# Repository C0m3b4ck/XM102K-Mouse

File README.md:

# XM102K Mouse in KiCAD 
[@PrinterFixer](https://www.youtube.com/@PrinterFixer)
[Video title here](VIDEO HERE - IF THERE IS NONE THEN IT IS NOT DONE)

KiCAD project with GERBER and DRILL files of the XM102K mouse PCB from 2012/02/03, remade manually by me, C0m3b4ck. All models of all components are in place, the PCB is of accurate size. The only inacurracies are the connections, which aren't 1:1 to the actual PCB. The microswitch and the rotary encoder are the exact same but from different companies (couldn't find original companies).

**The mouse PCB is from 2012/02/03. It is end-of-life and comes from an unknown Chinese manufacturer.** 

## Capabilities
**From the MX8733B documentation:**
* Optical Navigation Technology
* Universal Serial Bus Specification, version 2.0
* USB HID Specification, version 1.1
* USB-IF and WHQL compliable
* 5V Power Supply
* Power saving during no motion
* On chip LED drive with regulated current
* Crystal-less
* 1000CPI resolution (Counts per Inch)
* Low electromagnetic inference radiation
* Supports 3D (X, Y, Z) input
* Supports 3 buttons and mechanical wheel encoding

## GERBER, DRILL and BOM (click to download)
* [Full labelling and components](https://github.com/C0m3b4ck/XM102K-Mouse/blob/main/XM102K-GERBER-DRILL-FULL.7z)
* [Only soldered compoenents](https://github.com/C0m3b4ck/XM102K-Mouse/blob/main/XM102K-GERBER-DRILL.7z)
* [Bill of Materials in .CSV](https://github.com/C0m3b4ck/XM102K-Mouse/blob/main/XM102K-BOM.csv)
## Components:
* MX8733B IC - [documentation included](https://github.com/C0m3b4ck/XM102K-Mouse/blob/main/DOCS/MX8733B.pdf),
* Illinois KXM Capacitor 100uf - [documentation included](https://github.com/C0m3b4ck/XM102K-Mouse/blob/main/DOCS/Omron-D2F-01-A-datasheet.pdf),
* 68ohm resistor,
* Omron D2F-01 microswitch - [documentation included](https://github.com/C0m3b4ck/XM102K-Mouse/blob/main/DOCS/Omron-D2F-01-A-datasheet.pdf) (same as on PCB but from a different company),
* 2-pin LED,
* 3-pin AlpsAlpine Rotary Encoder,

## Repository layout

- `DOCS/` — component datasheets and board photos.
- mouse1/mouse1/mouse1-1/mouse1-1.kicad_pro - project file.
- `XM102K-GERBER-DRILL.7z` — archived Gerber/drill package.
- `Xtreme-XM102K/` — KiCAD project files - models, footprints, symbols, schematic and PCB.

## Images
| | | | |
|---|---|---|---|
| <div align="center"><br><sub>PCB 3D view in KiCAD - underside.</sub></div> | <div align="center"><br><sub>PCB 3D view in KiCAD - top view.</sub></div> | <div align="center"><br><sub>PCB 3D view in KiCAD - left.</sub></div> | <div align="center"><br><sub>PCB 3D view in KiCAD - right.</sub></div> |
| <div align="center"><br><sub>The underside of the PCB.</sub></div> | <div align="center"><br><sub>View of the PCB from top.</sub></div> | <div align="center"><br><sub>View of the PCB from the left.</sub></div> | <div align="center"><br><sub>View of the PCB from the right.</sub></div> |
| <div align="center"><br><sub>The mouse case, stock photo.</sub></div> | <div align="center"><br><sub>Full mouse case and cable view from top.</sub></div> |  |  |
| <div align="center"><br><sub>Schematic divided into sections.</sub></div> | <div align="center"><br><sub>Schematic of full circuit.</sub></div> |  |  |

## Credits

**Project made manually by me on 7/07/2026.**
* Alpine Rotary Encoder from [AlpsAlpine](https://www.alpsalpine.com/j/)
* D2F-01 microswitch from [Omron](https://www.omron.com/global/en/),
* KXM Capacitor from Illinois capacitor (website shut down),
* MX8733B mouse chip from [Shenzhen LIZE Electronic Technology Co., Ltd](http://www.lizhiic.com/)

## Purpose

This repository preserves the complete investigation of the XM102K mouse hardware: project files, documentation and images.
It is intended as a technical reference for anyone analyzing, repairing, or getting inspired by the XM102K design and the MX8733B-based optical mouse architecture.

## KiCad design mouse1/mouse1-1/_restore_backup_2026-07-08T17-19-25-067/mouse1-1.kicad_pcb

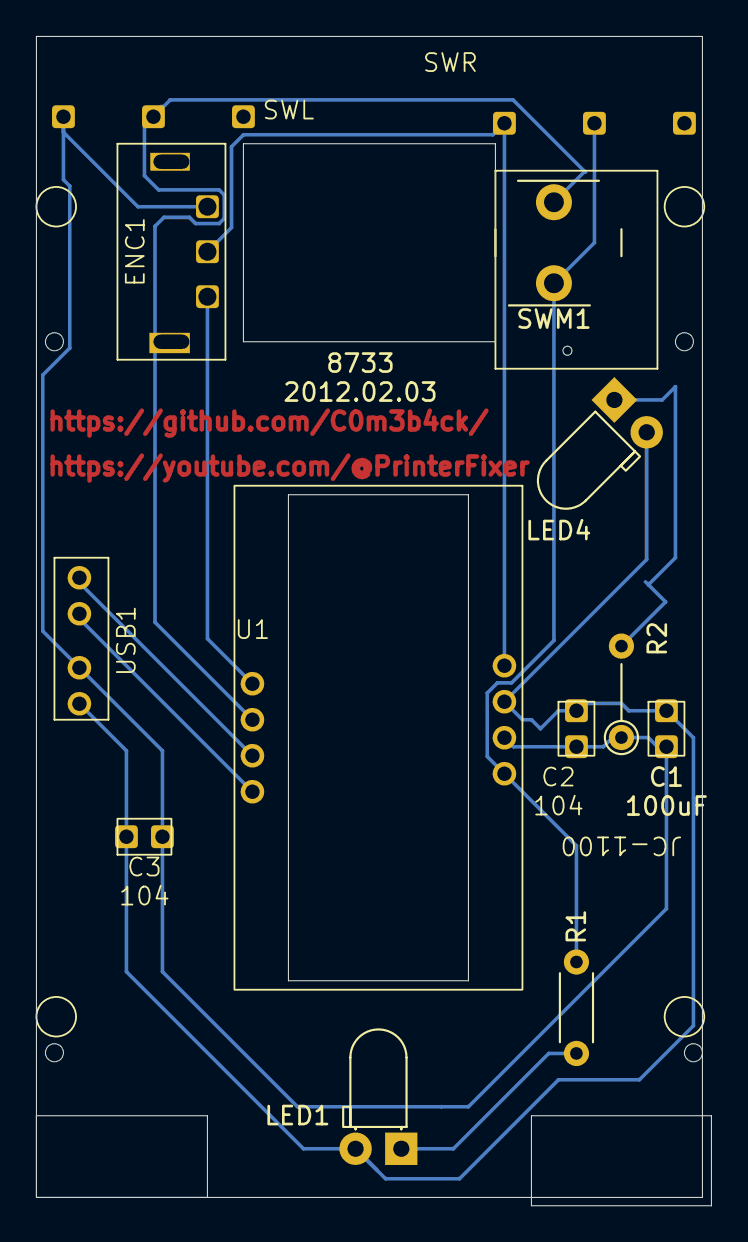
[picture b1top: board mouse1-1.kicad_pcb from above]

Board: 2 copper layers, 37.0 x 64.5 mm, 13 parts (0 on the bottom side), 9 nets.

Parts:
C1, C2, C3: SmallCapacitor
D2: VCC_LED; LED_D3.0mm_Horizontal_O1.27mm_Z2.0mm
ENC1: AlpineRotaryEncoder
LED1: LED; LED_D3.0mm_Horizontal_O1.27mm_Z2.0mm
R1: 68 ohm; R_Axial_DIN0204_L3.6mm_D1.6mm_P5.08mm_Horizontal
R2: R; R_Axial_DIN0204_L3.6mm_D1.6mm_P5.08mm_Vertical
SWL: D2FT_SW
SWM1: SW_Push; SW_PUSH_6mm_h7.3mm
SWR: D2FT_SW
U1: MX8733B IC
USB1: USB_diredt_wire

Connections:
unnamed: C1.1 (GND), C2.1 (GND), C3.1 (GND), D2.1 (A), ENC1.3 (C), R2.1, R2.2, SWL.1 (C), U1.7 (VDD), USB1.4 (VCC)
unnamed: C1.2 (VCC), C2.2 (VCC), C3.2 (VCC), D2.2 (K), LED1.2 (A), U1.6 (GND), USB1.3 (GND)
unnamed: LED1.1 (K), R1.2
unnamed: ENC1.2 (B), SWR.1 (C), U1.8 (SK1)
unnamed: ENC1.1 (A), U1.1 (SK2)
unnamed: SWL.2 (NO), SWM1.1, U1.2 (SK0)
unnamed: R1.1, SWM1.2, SWR.2 (NO), U1.5 (LED)
unnamed: U1.4 (DM), USB1.2 (D)
unnamed: U1.3 (DP), USB1.1 (C)
